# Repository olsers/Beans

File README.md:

# Beans
> what should I call my new keyboard project floss? Beans.

This is my working space for the Ergogen > kiCAD workflow.

## Progress:

### BeansV1
- Used Ergopad to create a rough mapping of where my fingers should go.
- Created an Ergogen yaml (relying heavily on work by flatfootfox and the Caldera).
- Set up the local Ergogen environment so running a commmand would generate a KiCAD PCB file with included footprints.
- Routed traces between everthing.
- Sent two halves of to JLCPCB to get made.
- Soldered all the components onto it (diodes, hotswap sockets, mill max pins and sockets, controllers, button, switch, battery header)
- Figure out how to create a ZMK firmware after much trial and error, and managed to flash both halves of keyboard. (currently typing this out on beans!)
- OUTSTANDING: afix the batteries and connect via bluetooth.

**Learnings thus far**
- The inter-column finger splay is extreme and actually quite uncomporable.
- The 5th thumbkey is probably redundant.
- The general spacing between keys should be a bit tighter.
- I should figure out how to get both sides made as one snap-off-able pcb.
- Mod-tap is wicked difficult to wrap my head around - currently only using shift/D.
- I should also figure out how to add holes for tenting. Also extra pcbs as baseplates.
- A soldering iron to a keycap makes a surprisingly effective homeing dot.

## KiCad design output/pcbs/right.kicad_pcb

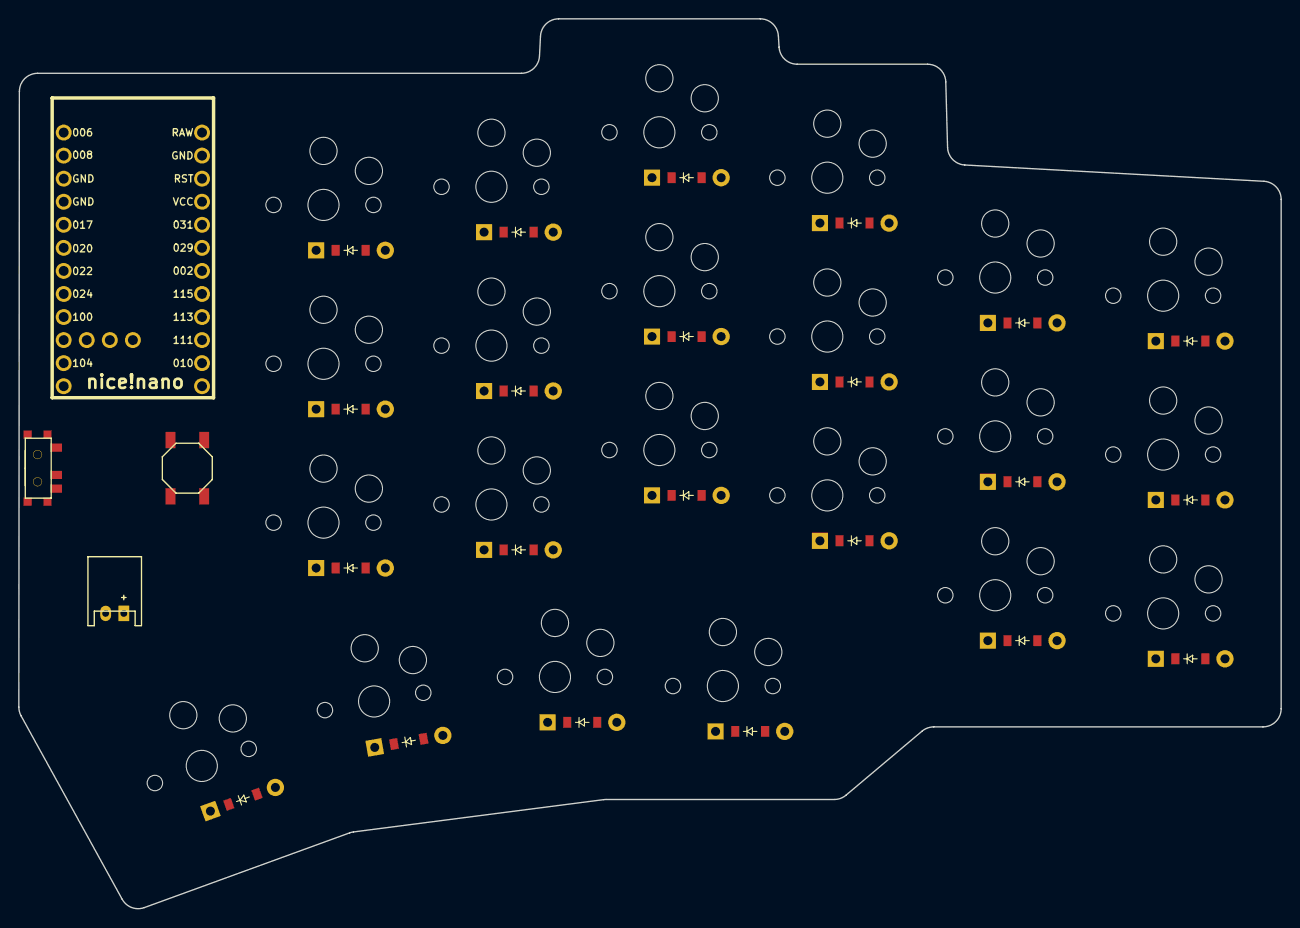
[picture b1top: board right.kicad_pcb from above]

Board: 2 copper layers, 139.1 x 98.0 mm, 48 parts (0 on the bottom side), 36 nets, no tracks yet.

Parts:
B1: SW_TACT_ALPS_SKQGABE010
D1, D2, D3, D4, D5, D6, D7, D8, D9, D10, D11, D12, D13, D14, D15, D16, D17, D18, D19, D20, D21, D22: ComboDiode
JST1: JST_PH_S2B-PH-K_02x2.00mm_Angled
MCU1: nice_nano
S1, S2, S3, S4, S5, S6, S7, S8, S9, S10, S11, S12, S13, S14, S15, S16, S17, S18, S19, S20, S21, S22: PG1350
T1: SPDT_C128955

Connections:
GND: B1.1, JST1.2, MCU1.3, MCU1.4, MCU1.23
P002: MCU1.18, S10.1, S11.1, S12.1, S20.1
P009: D1.1, D4.1, D7.1, D10.1, D13.1, D16.1, MCU1.13
P010: D2.1, D5.1, D8.1, D11.1, D14.1, D17.1, MCU1.14
P029: MCU1.19, S13.1, S14.1, S15.1, S21.1
P031: MCU1.20, S16.1, S17.1, S18.1, S22.1
P104: MCU1.11, S1.1, S2.1, S3.1
P106: D19.1, D20.1, D21.1, D22.1, MCU1.12
P111: D3.1, D6.1, D9.1, D12.1, D15.1, D18.1, MCU1.15
P113: MCU1.16, S4.1, S5.1, S6.1
P115: MCU1.17, S7.1, S8.1, S9.1, S19.1
RAW: MCU1.24, T1.2
RST: B1.2, MCU1.22
mirror_fifth_bottom: D13.2, S13.2
mirror_fifth_home: D14.2, S14.2
mirror_fifth_top: D15.2, S15.2
mirror_first_bottom: D1.2, S1.2
mirror_first_home: D2.2, S2.2
mirror_first_only: D19.2, S19.2
mirror_first_top: D3.2, S3.2
mirror_fourth_bottom: D10.2, S10.2
mirror_fourth_home: D11.2, S11.2
mirror_fourth_only: D22.2, S22.2
mirror_fourth_top: D12.2, S12.2
mirror_second_bottom: D4.2, S4.2
mirror_second_home: D5.2, S5.2
mirror_second_only: D20.2, S20.2
mirror_second_top: D6.2, S6.2
mirror_sixth_bottom: D16.2, S16.2
mirror_sixth_home: D17.2, S17.2
mirror_sixth_top: D18.2, S18.2
mirror_third_bottom: D7.2, S7.2
mirror_third_home: D8.2, S8.2
mirror_third_only: D21.2, S21.2
mirror_third_top: D9.2, S9.2
pos: JST1.1, T1.1

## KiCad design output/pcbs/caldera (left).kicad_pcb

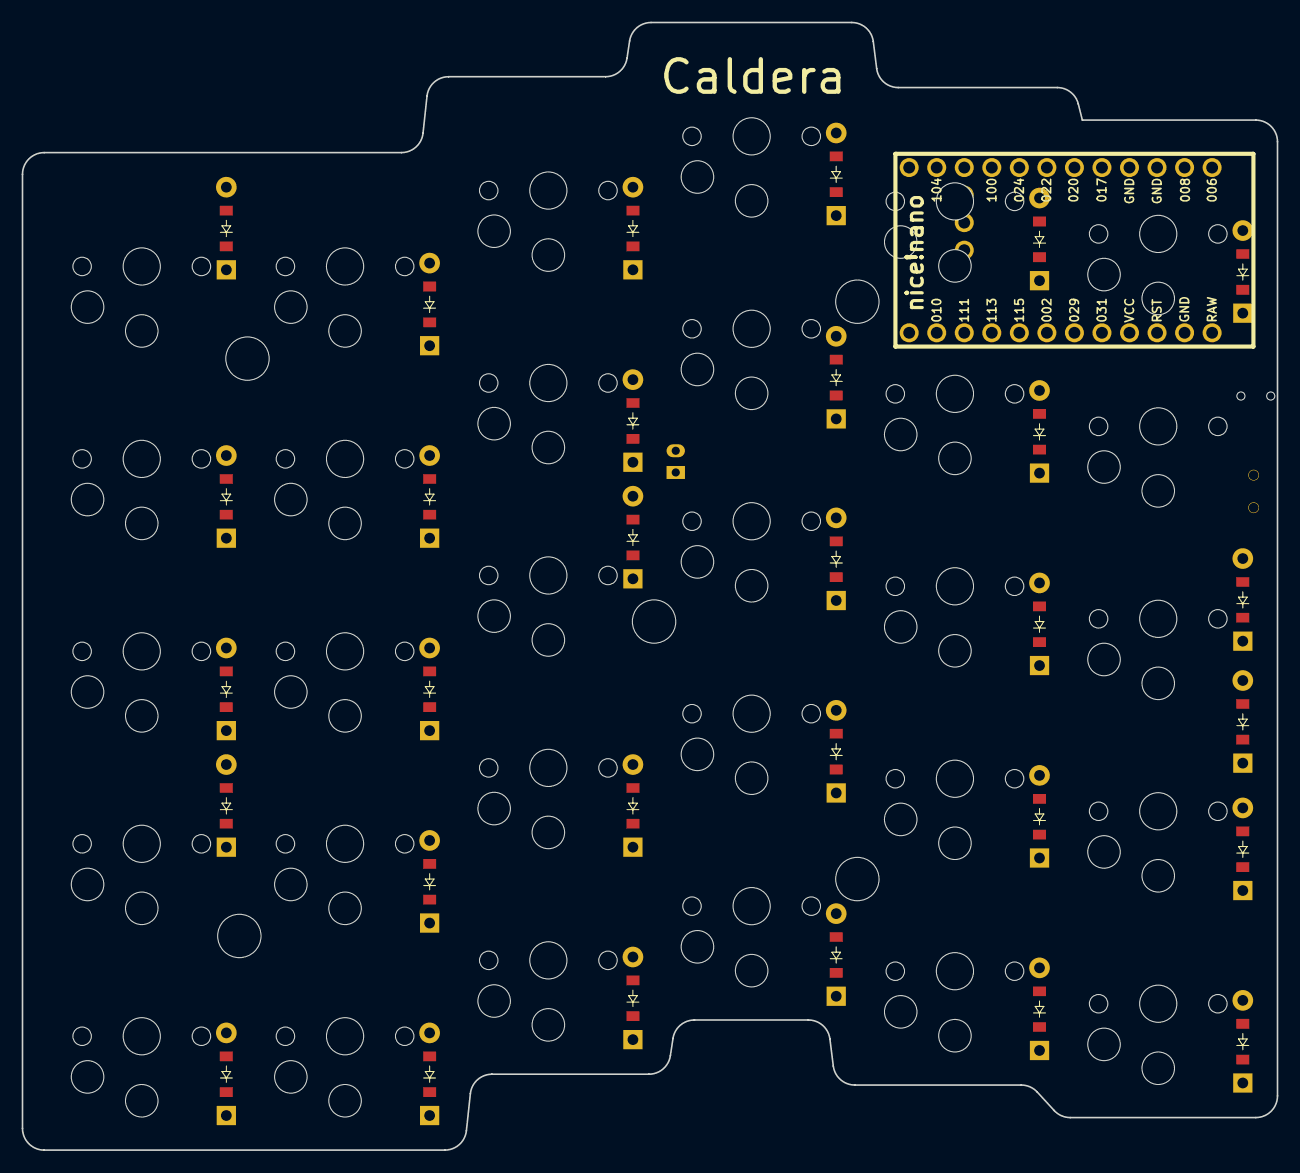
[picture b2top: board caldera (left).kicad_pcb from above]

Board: 2 copper layers, 115.8 x 104.0 mm, 64 parts (0 on the bottom side), 45 nets, no tracks yet.

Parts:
B1: Panasonic_EVQPUL_EVQPUC
D1, D2, D3, D4, D5, D6, D7, D8, D9, D10, D11, D12, D13, D14, D15, D16, D17, D18, D19, D20, D21, D22, D23, D24, D25, D26, D27, D28, D29, D30: ComboDiode
JST1: JST_PH_S2B-PH-K_02x2.00mm_Angled
MCU1: nice_nano
S1, S2, S3, S4, S5, S6, S7, S8, S9, S10, S11, S12, S13, S14, S15, S16, S17, S18, S19, S20, S21, S22, S23, S24, S25, S26, S27, S28, S29, S30: PG1350
T1: SPDT_C128955

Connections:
GND: B1.1, JST1.2, MCU1.3, MCU1.4, MCU1.23
P002: D2.1, D6.1, D14.1, D18.1, D25.1, D28.1, MCU1.18
P011: MCU1.10, S21.1, S22.1, S23.1, S24.1, S25.1
P017: MCU1.5, S26.1, S27.1, S28.1, S29.1, S30.1
P020: MCU1.6, S1.1, S2.1, S3.1, S4.1, S5.1
P022: MCU1.7, S6.1, S7.1, S8.1, S9.1, S10.1
P024: MCU1.8, S11.1, S12.1, S13.1, S14.1, S15.1
P029: D3.1, D7.1, D11.1, D19.1, D24.1, D30.1, MCU1.19
P031: D8.1, D12.1, D15.1, D20.1, D23.1, D27.1, MCU1.20
P100: MCU1.9, S16.1, S17.1, S18.1, S19.1, S20.1
P113: D1.1, D4.1, D9.1, D16.1, D21.1, D29.1, MCU1.16
P115: D5.1, D10.1, D13.1, D17.1, D22.1, D26.1, MCU1.17
RAW: MCU1.24, T1.2
RST: B1.2, MCU1.22
fifth_bottom: D17.2, S22.2
fifth_home: D18.2, S23.2
fifth_mod: D16.2, S21.2
fifth_num: D20.2, S25.2
fifth_top: D19.2, S24.2
first_bottom: D26.2, S2.2
first_home: D2.2, S3.2
first_mod: D1.2, S1.2
first_num: D27.2, S5.2
first_top: D3.2, S4.2
fourth_bottom: D13.2, S17.2
fourth_home: D14.2, S18.2
fourth_mod: D29.2, S16.2
fourth_num: D15.2, S20.2
fourth_top: D30.2, S19.2
pos: JST1.1, T1.1
second_bottom: D5.2, S7.2
second_home: D6.2, S8.2
second_mod: D4.2, S6.2
second_num: D8.2, S10.2
second_top: D7.2, S9.2
sixth_bottom: D22.2, S27.2
sixth_home: D25.2, S28.2
sixth_mod: D21.2, S26.2
sixth_num: D23.2, S30.2
sixth_top: D24.2, S29.2
third_bottom: D10.2, S12.2
third_home: D28.2, S13.2
third_mod: D9.2, S11.2
third_num: D12.2, S15.2
third_top: D11.2, S14.2

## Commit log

2024-08-16 Updated the wip V2 yaml to say so
2024-08-16 Added a readme and the notes and progress thus far.
2024-08-16 Removed vscode workspace file
2024-08-16 Fixed some header issues
2024-08-16 Removed line
2024-08-19 Added some helpful V1 images
2024-08-21 More work on V2
2024-09-01 A load of v2 stuff
